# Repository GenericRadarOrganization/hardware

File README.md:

# hardware
Design Files for Radar Board. Including Kicad Project and Individual Schematics

# Program Requirements
* KiCAD : http://kicad-pcb.org/download/
* GitDesktop (Optional) : https://desktop.github.com/

# How to Operate:
1. Checkout Repositiory
2. Open the "Radar.pro"
3. Find the Schemtatic of which you are responsible for and do your work within that
4. Commit and push your changes, making sure you only changed your schematic
5. Make sure to Pull before you begin edditing

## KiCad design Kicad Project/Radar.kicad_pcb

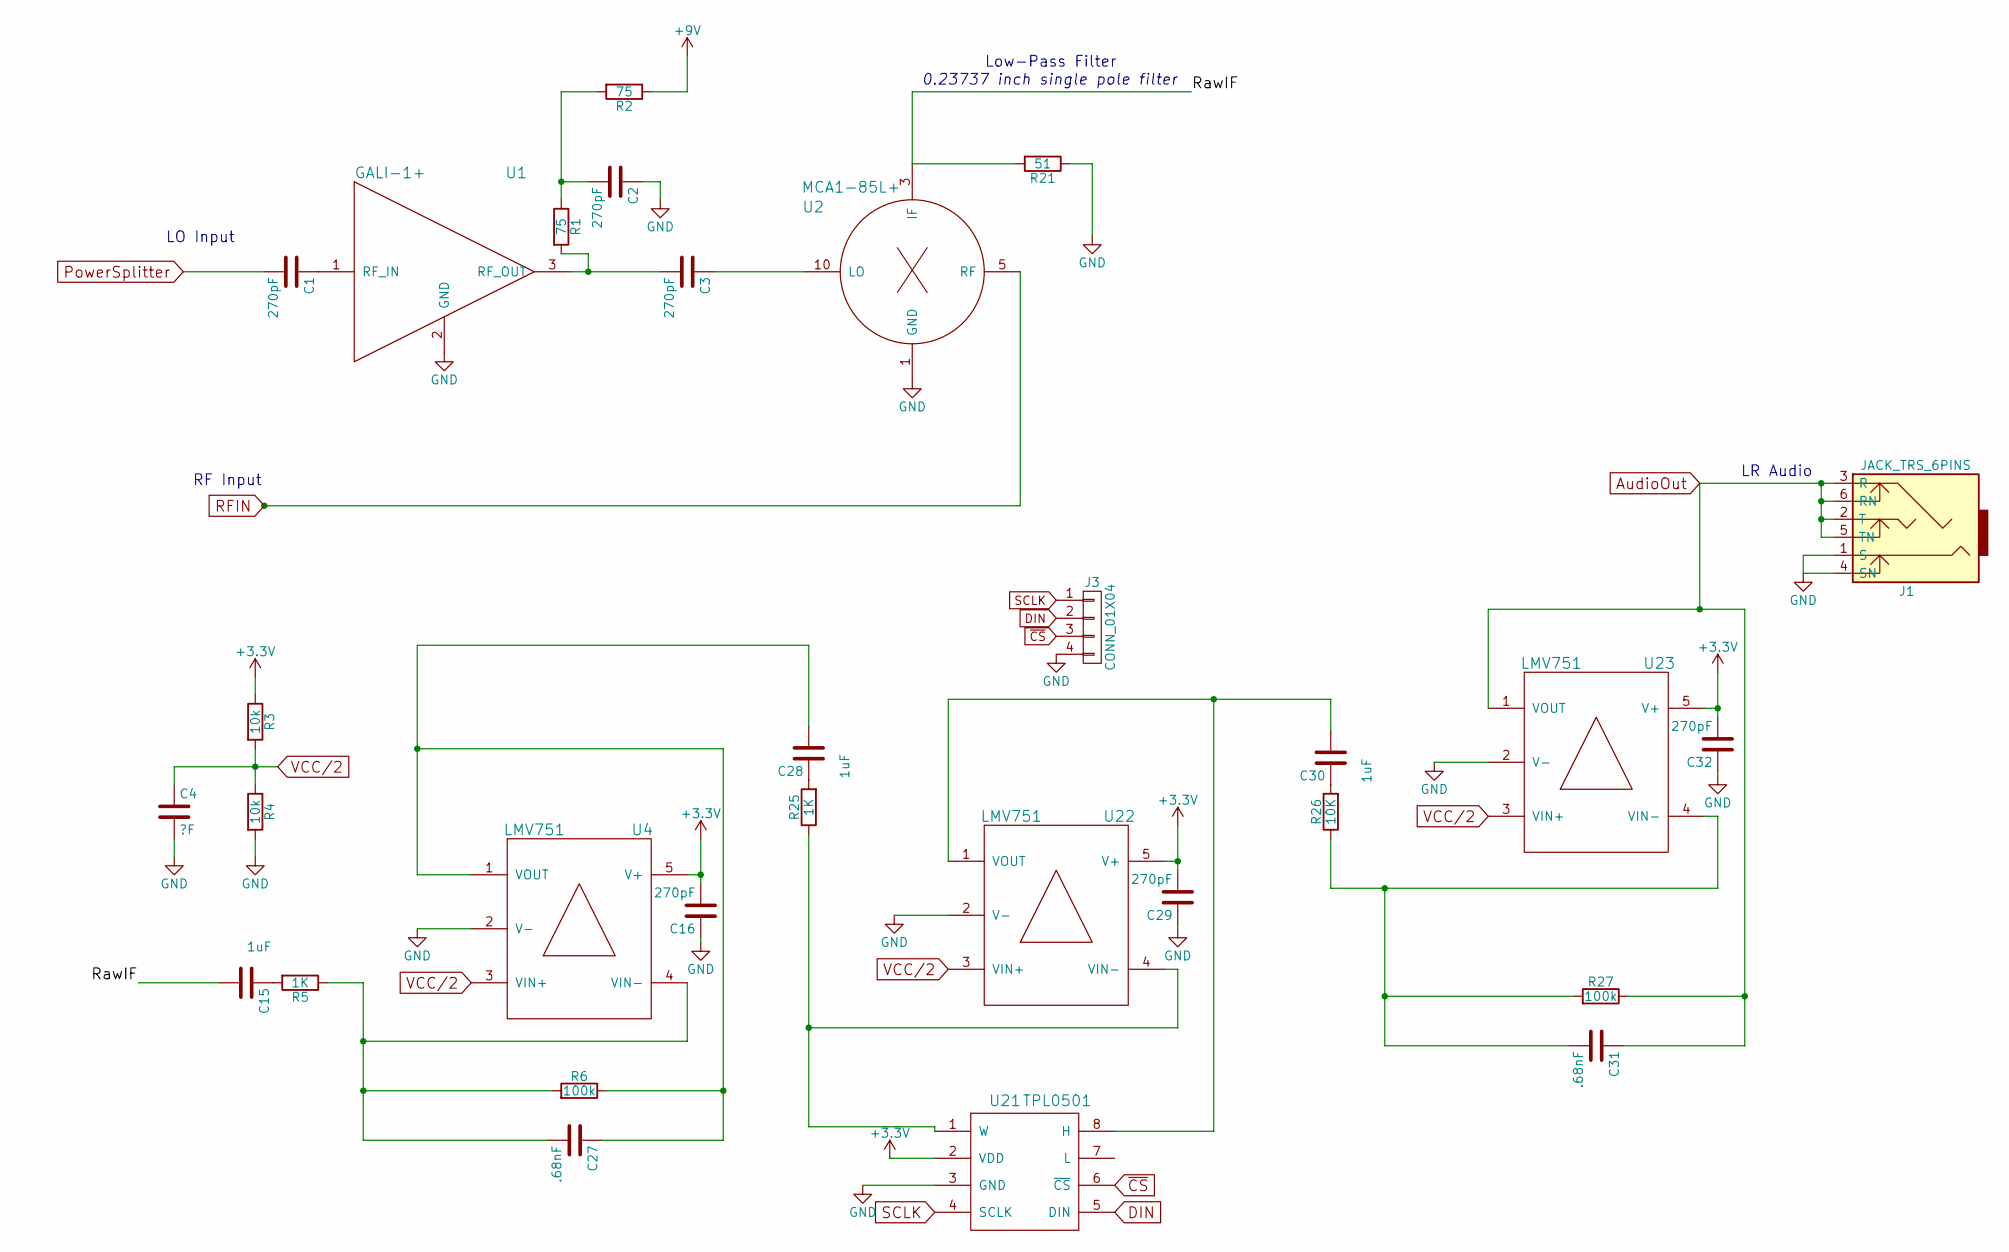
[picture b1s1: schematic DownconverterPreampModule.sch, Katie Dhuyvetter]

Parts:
C1, C3: 270pF; 100PAD
C2: 270pF; 100PAD+GND3
C4: ?F; C_0603
C15, C28, C30: 1uF; C_0603
C16, C29, C32: 270pF; C_0603
C27, C31: .68nF; C_0603
J1: JACK_TRS_6PINS; 3.5mm_SMD
J3: CONN_01X04; Pin_Header_Straight_1x04_Pitch2.54mm
R1: 75; 100PAD
R2: 75; 100PAD+GND
R3, R4: 10k; R_0603
R5, R25: 1K; R_0603
R6, R27: 100k; R_0603
R21: 51; R_0603
R26: 10K; R_0603
U1: GALI-1+; Amplifier
U2: MCA1-85L+; DZ885
U4, U22, U23: LMV751; SOT23-5
U21: TPL0501; SOT-23(8)

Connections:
+3V3: C16.2, C29.2, C32.2, R3.1, U4.5 (V+), U21.2 (VDD), U22.5 (V+), U23.5 (V+); also elsewhere on the board
+9V: R2.1; also elsewhere on the board
/DownconverterPreampModule/RawIF: C15.2, R21.2, U2.3 (IF)
AudioOut: C31.1, J1.2 (T), J1.3 (R), J1.5 (TN), J1.6 (RN), R27.1, U23.1 (VOUT); also elsewhere on the board
DIN: J3.2, U21.5 (DIN)
GND: C2.1, C4.2, C16.1, C29.1, C32.1, J1.1 (S), J1.4 (SN), J3.4, R4.2, R21.1, U1.2 (GND), U2.1 (GND), U2.2, U2.4, U2.6, U2.7, U2.8, U2.9, U4.2 (V-), U21.3 (GND), U22.2 (V-), U23.2 (V-); also elsewhere on the board
unnamed: C1.1, U1.1 (RF_IN)
unnamed: C2.2, R1.1, R2.2
unnamed: C3.1, U2.10 (LO)
unnamed: C3.2, R1.2, U1.3 (RF_OUT)
unnamed: C15.1, R5.2
unnamed: C27.1, C28.2, R6.1, U4.1 (VOUT)
unnamed: C27.2, R5.1, R6.2, U4.4 (VIN-)
unnamed: C28.1, R25.2
unnamed: C30.1, R26.2
unnamed: C30.2, U21.8 (H), U22.1 (VOUT)
unnamed: C31.2, R26.1, R27.2, U23.4 (VIN-)
unnamed: R25.1, U21.1 (W), U22.4 (VIN-)
PowerSplitter: C1.2; also elsewhere on the board
RFIN: U2.5 (RF); also elsewhere on the board
SCLK: J3.1, U21.4 (SCLK)
VCC/2: C4.1, R3.2, R4.1, U4.3 (VIN+), U22.3 (VIN+), U23.3 (VIN+)
~CS: J3.3, U21.6 (~CS)

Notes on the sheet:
LO Input
RF Input
Low-Pass Filter
0.23737 inch single pole filter
LR Audio

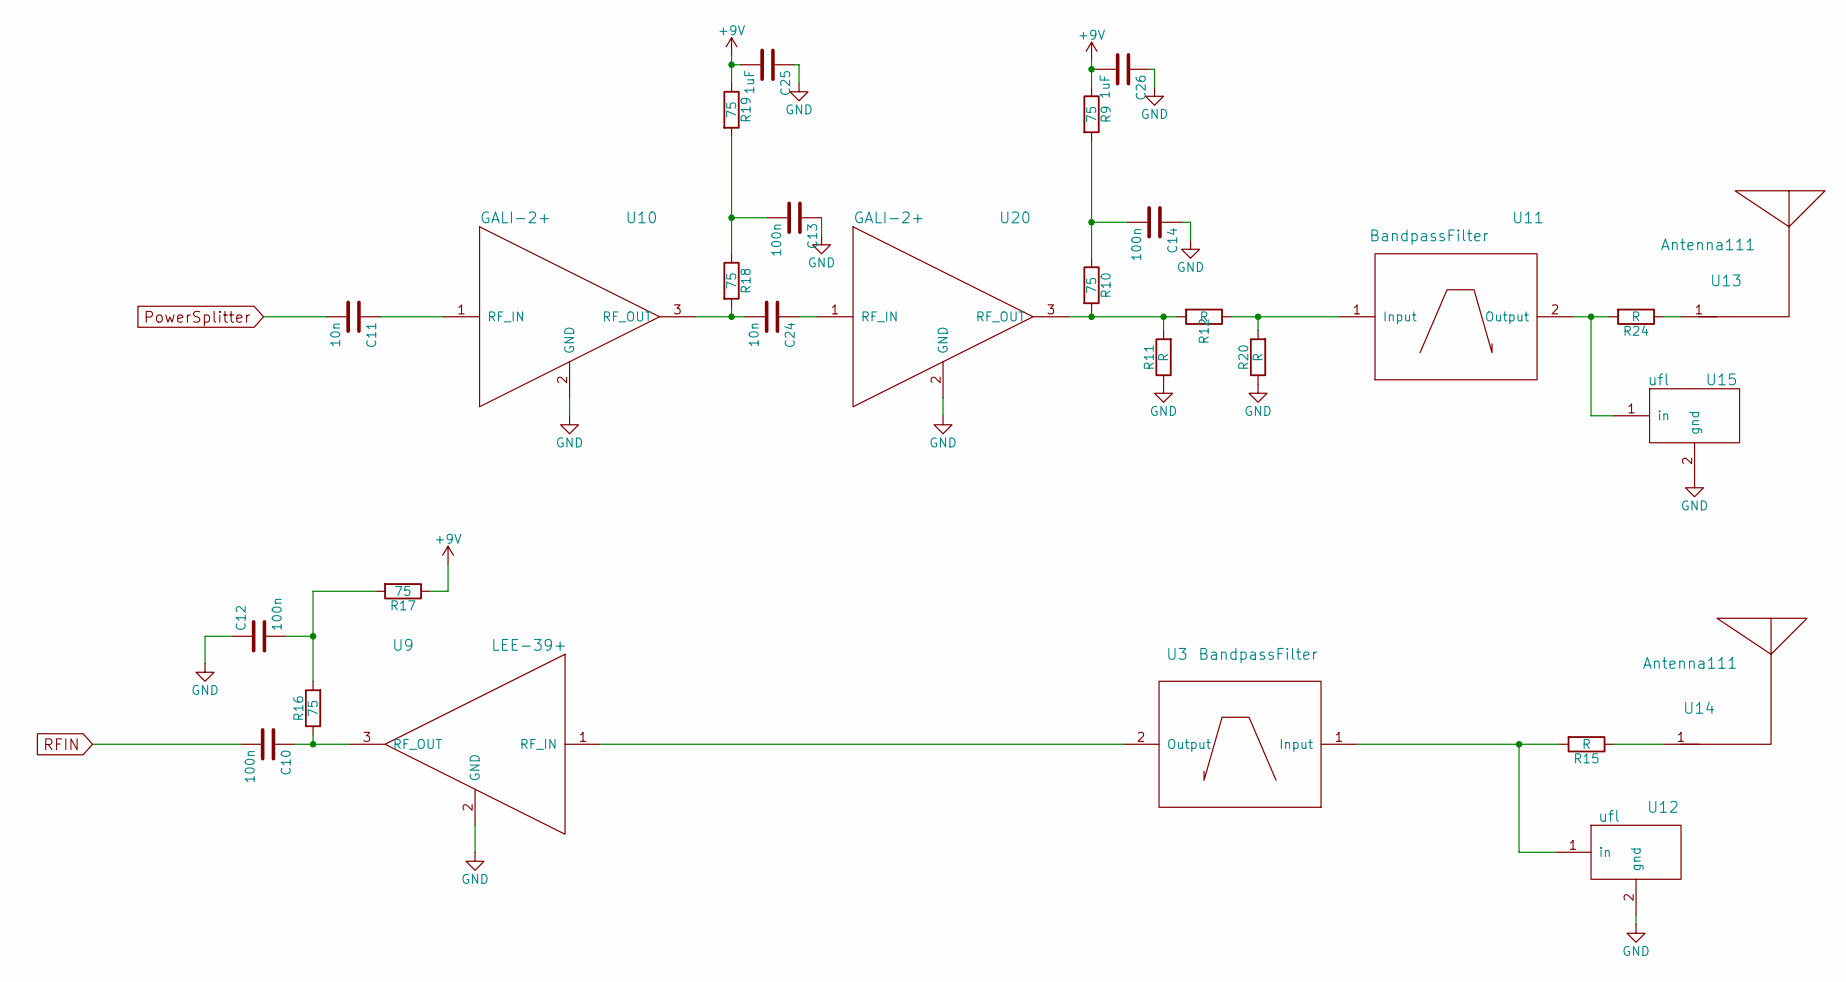
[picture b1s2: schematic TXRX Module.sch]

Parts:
C10: 100n; 100PAD
C11, C24: 10n; 100PAD
C12, C13, C14: 100n; 100PAD+GND3
C25, C26: 1uF; C_0603
R9, R19: 75; 100PAD+GND2
R10, R16, R18: 75; 100PAD
R11, R20: R; 100PAD+GND2
R12, R15, R24: R; 100PAD
R17: 75; 100PAD+GND
U3: BandpassFilter; QuadPoleFilterMirror
U9: LEE-39+; Amplifier
U10, U20: GALI-2+; Amplifier
U11: BandpassFilter; QuadPoleFilter
U12, U15: ufl; UFL
U13, U14: Antenna111; patch58

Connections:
+9V: C25.2, C26.2, R9.1, R17.1, R19.1; also elsewhere on the board
GND: C12.1, C13.1, C14.1, C25.1, C26.1, R11.1, R20.1, U9.2 (GND), U10.2 (GND), U12.2 (gnd), U15.2 (gnd), U20.2 (GND); also elsewhere on the board
unnamed: C10.1, R16.1, U9.3 (RF_OUT)
unnamed: C11.1, U10.1 (RF_IN)
unnamed: C12.2, R16.2, R17.2
unnamed: C13.2, R18.1, R19.2
unnamed: C14.2, R9.2, R10.1
unnamed: C24.1, U20.1 (RF_IN)
unnamed: C24.2, R18.2, U10.3 (RF_OUT)
unnamed: R10.2, R11.2, R12.2, U20.3 (RF_OUT)
unnamed: R12.1, R20.2, U11.1 (Input)
unnamed: R15.1, U14.1
unnamed: R15.2, U3.1 (Input), U12.1 (in)
unnamed: R24.1, U13.1
unnamed: R24.2, U11.2 (Output), U15.1 (in)
unnamed: U3.2 (Output), U9.1 (RF_IN)
PowerSplitter: C11.2; also elsewhere on the board
RFIN: C10.2; also elsewhere on the board

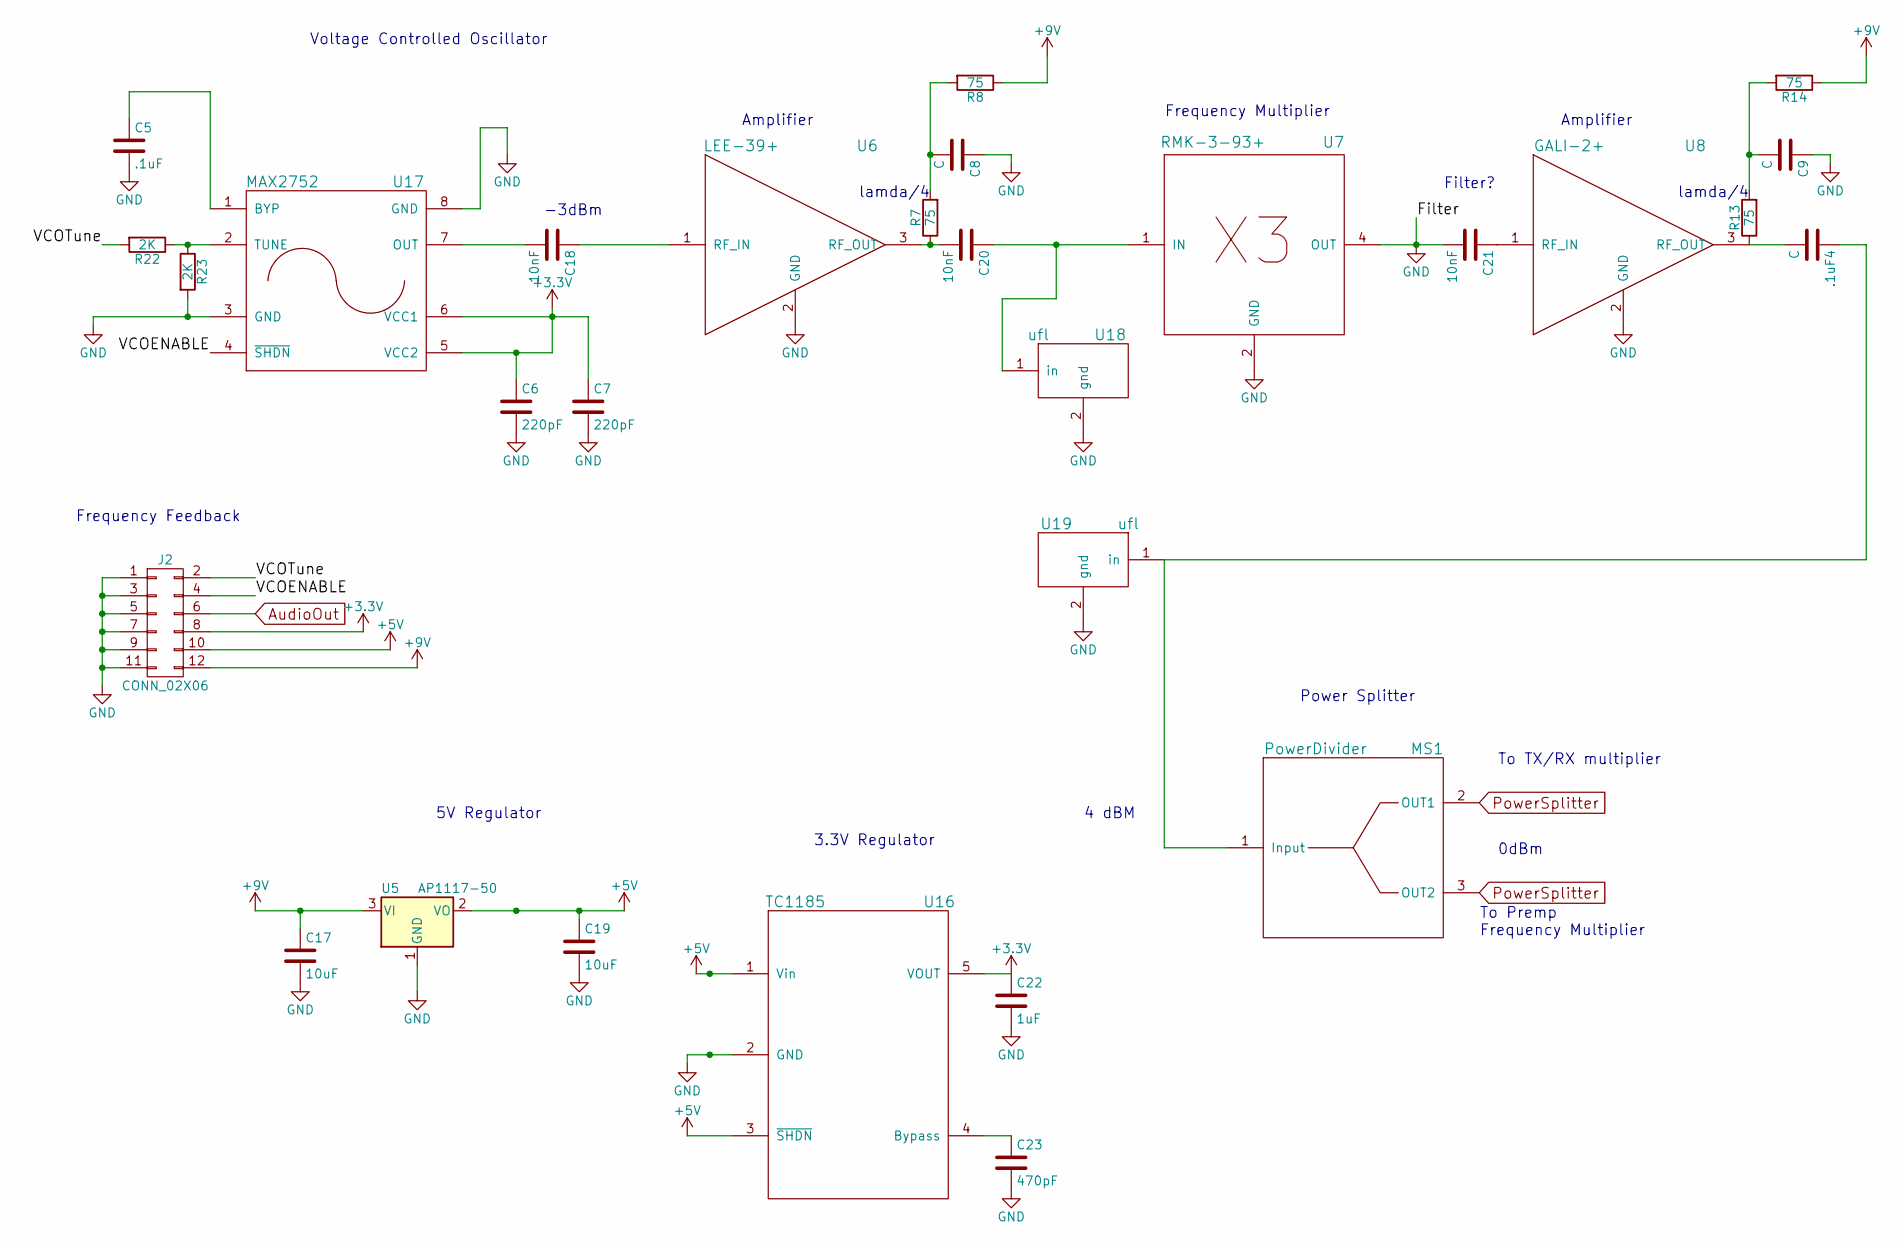
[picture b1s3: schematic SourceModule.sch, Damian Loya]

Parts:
.1uF4: C; 100PAD
C5: .1uF; C_0603
C6, C7: 220pF; C_0603
C8, C9: C; 100PAD+GND3
C17: 10uF; C_0805
C18, C20, C21: 10nF; 100PAD
C19: 10uF; C_1210_HandSoldering
C22: 1uF; C_1210_HandSoldering
C23: 470pF; C_0805
J2: CONN_02X06; Pin_Header_Straight_2x06_Pitch2.54mm
MS1: PowerDivider; powersplitter2
R7, R13: 75; 100PAD
R8, R14: 75; 100PAD+GND
R22, R23: 2K; R_0603
U5: AP1117-50; ZLDO1117
U6: LEE-39+; Amplifier
U7: RMK-3-93+; TT1224
U8: GALI-2+; Amplifier
U16: TC1185; SOT23-5
U17: MAX2752
U18, U19: ufl; UFL

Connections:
+3V3: C6.1, C7.1, C22.1, J2.8, U16.5 (VOUT), U17.5 (VCC2), U17.6 (VCC1); also elsewhere on the board
+5V: C19.1, J2.10, U5.2 (VO), U16.1 (Vin), U16.3 (~SHDN)
+9V: C17.1, J2.12, R8.1, R14.1, U5.3 (VI); also elsewhere on the board
/SourceModule.sch/VCOENABLE: J2.4, U17.4 (~SHDN)
/SourceModule.sch/VCOTune: J2.2, R22.2
AudioOut: J2.6; also elsewhere on the board
GND: C5.2, C6.2, C7.2, C8.1, C9.1, C17.2, C19.2, C21.2, C22.2, C23.2, J2.1, J2.3, J2.5, J2.7, J2.9, J2.11, R23.2, U5.1 (GND), U6.2 (GND), U7.2 (GND), U7.3, U7.4 (OUT), U7.5, U7.6, U8.2 (GND), U16.2 (GND), U17.3 (GND), U17.8 (GND), U18.2 (gnd), U19.2 (gnd); also elsewhere on the board
unnamed: .1uF4.1, MS1.1 (Input), U19.1 (in)
unnamed: .1uF4.2, R13.1, U8.3 (RF_OUT)
unnamed: C5.1, U17.1 (BYP)
unnamed: C8.2, R7.2, R8.2
unnamed: C9.2, R13.2, R14.2
unnamed: C18.1, U6.1 (RF_IN)
unnamed: C18.2, U17.7 (OUT)
unnamed: C20.1, U7.1 (IN), U18.1 (in)
unnamed: C20.2, R7.1, U6.3 (RF_OUT)
unnamed: C21.1, U8.1 (RF_IN)
unnamed: C23.1, U16.4 (Bypass)
unnamed: R22.1, R23.1, U17.2 (TUNE)
PowerSplitter: MS1.2 (OUT1), MS1.3 (OUT2); also elsewhere on the board

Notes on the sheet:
Voltage Controlled Oscillator
Amplifier
Frequency Multiplier
Power Splitter
To Premp Frequency Multiplier
To TX/RX multiplier
Frequency Feedback
0dBm
-3dBm
lamda/4
4 dBM
Filter?
5V Regulator
3.3V Regulator

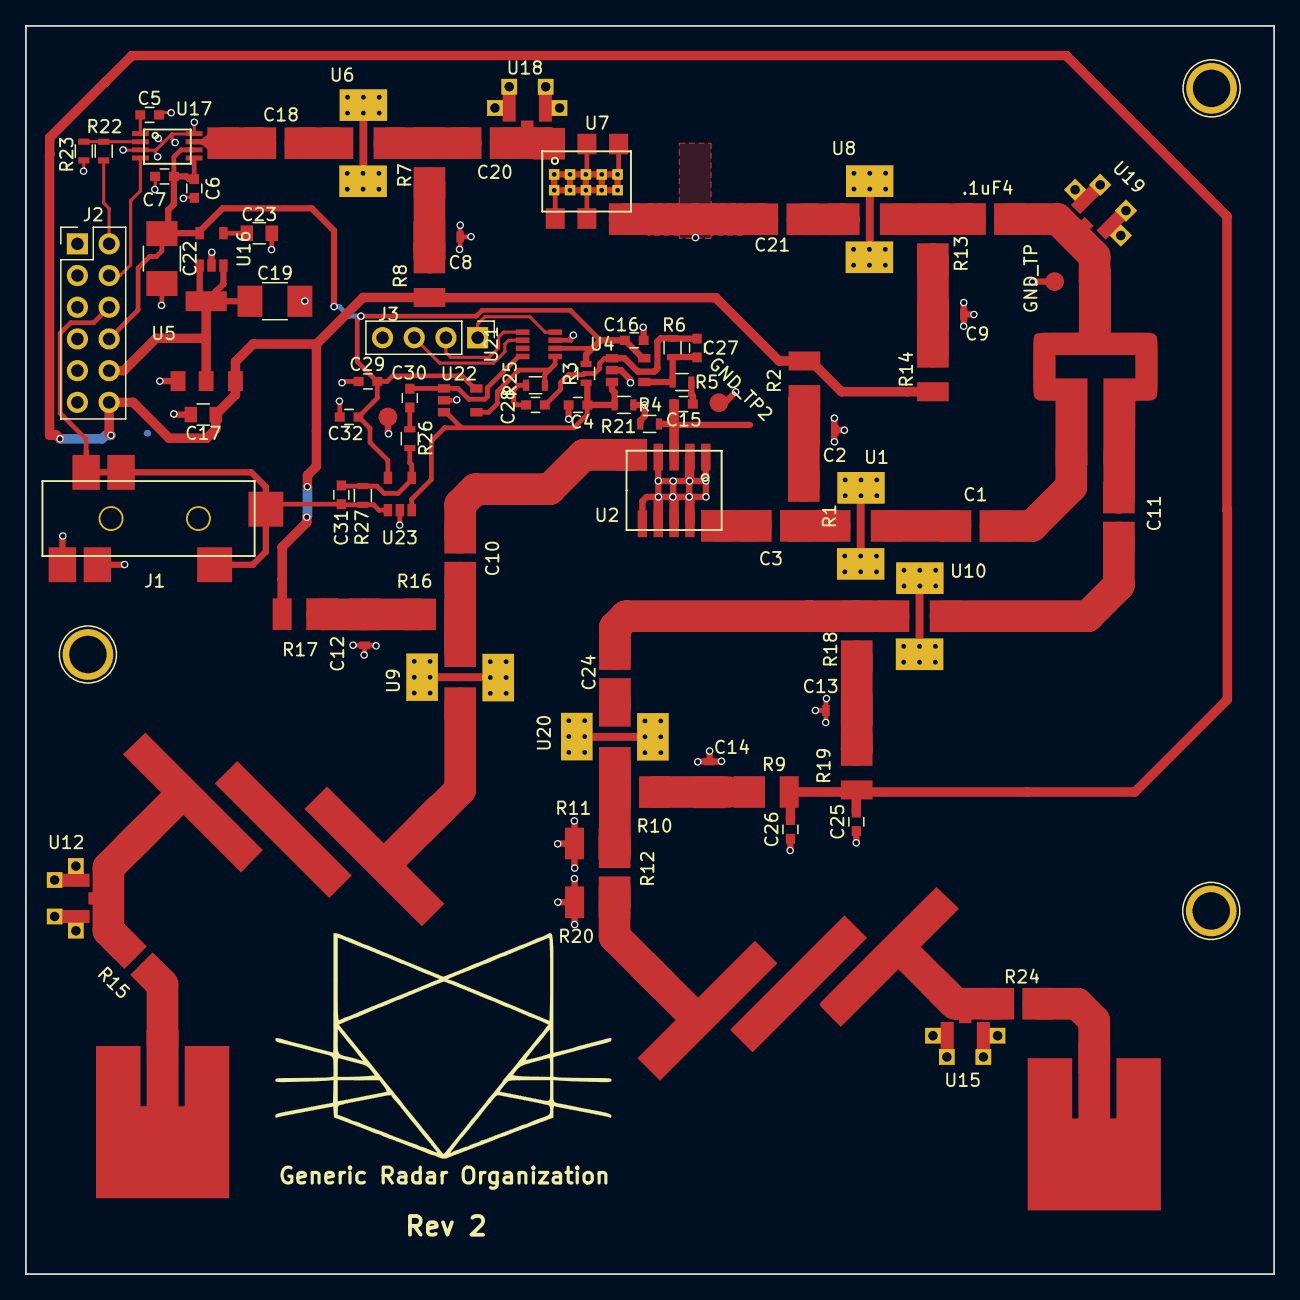
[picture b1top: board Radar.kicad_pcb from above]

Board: 2 copper layers, 100.0 x 100.0 mm, 89 parts (0 on the bottom side), 52 nets.

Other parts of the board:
GND_TP, GND_TP2: Measurement_Point_Round-SMD-Pad_Small

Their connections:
GND: GND_TP.1, GND_TP2.1; also elsewhere on the board

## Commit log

2017-10-25 Set up a hierarchy for the Source Module, Tx/RX Module, and DownConverter/Preamp Module
2017-10-25 Created a digital copy of the Project Assignment
2017-10-26 Added more components
2017-10-26 First edit.
2017-10-26 Damian edits
2017-10-26 Deleted Backup Files, Don't Commit/push these
2017-10-26 Add .gitignore
    Bet you can't commit backups now
2017-10-26 Update gitignore
    Prevents accidentally committing temp files, netlists, autorouter data
2017-10-26 Added Relative Path to footprint library
2017-10-28 Initial circuit setup
2017-10-28 Component Library linked Circuit work on Source Module
2017-10-30 Added Power calculations and resistive divider
2017-10-31 Change test
2017-10-31 Updated labels
2017-10-31 test of git desktop and kicad
2017-10-31 interconnects
2017-10-31 Added Hierarchical labels to TX/RX module
2017-10-31 Added ADS Workspaces
2017-10-31 Stuff
2017-10-31 Things.
2017-11-01 Added second amplifier.
2017-11-01 Messed with parts
2017-11-02 Reorganization
2017-11-05 Updated TxRx module schematic
2017-11-06 PCB 1
2017-11-06 added antennas and receive end
2017-11-06 Connected stuffs and things
2017-11-06 PCB Changes
2017-11-06 Filter edit.
2017-11-07 PCB and Schematic updates
2017-11-07 fixed merge error
2017-11-07 Added Net list to committed Files
2017-11-07 Added capacitor values and power rails
2017-11-07 PCB for source Module mostly complete, missing filter. Power Spliter still has issues.
    Some minor changes made to all schematics for the net lists to be properall connected
    A bunch of parts made
2017-11-07 PCB LAYOUT update
2017-11-08 asdf
2017-11-08 pcb stuff
2017-11-08 Added Filters to PCB
2017-11-08 added zero ohm resistors
2017-11-08 Added ufl connector to schematic
2017-11-08 added antennas to pcb
2017-11-08 Connected patch antennas, removed cap on rx side, added radial stub
2017-11-09 Added Documentation, Fixed Some Footprints
2017-11-10 More PCB Updates
2017-11-10 PCB Pre Flood
2017-11-10 Added GND Flood
2017-11-10 PCB Updates and added some Project outputs, like gerbers and schematic pdf
2017-11-10 Changed Routing of 9V line, added more documentation
2017-11-10 Gain Chart updated
2017-11-10 grammar and spelling
2017-11-10 Changed caps on tx rx to 100n
2017-11-10 Add firmware docs
2017-11-10 PCB Edits post PDR
2017-11-10 updated gerbers
2017-11-10 Rev 1!
    Gerbers Generated
    Sent to Smart
2017-11-10 Gerbers updated with correct file extensions
2017-11-28 Rev 2 update 1
    Changes for Rev2:
    Mounting Holes (duh)
    Right Headers
    HeadphoneJack
    Added tantulum Caps at Regulators
    Added UFL conns
2017-11-28 More Routing
2017-12-01 Updated tx/rx schematic for two amps on chains
2017-12-01 Damian's almost to rev 2 completion, needs audio amps
2017-12-02 Fixed Merge Stuff With TX/RX board
2017-12-02 Added some Gain calcs for the RX side
2017-12-03 Rev 2?
2017-12-03 New Gerbers, Shipped
